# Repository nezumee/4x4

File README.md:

# 4x4 keyboard
 
The 4x4 keyboard is a modular keyboard with per-key RGB lighting intended to be used as a base for prototyping MIDI controller with QMK firmware.

It consists of the following parts:
* Head PCB with MCU and other connectors
* 1 to 4 key PCB, each having 16 hotswap Cherry MX switches in 4x4 layout

These parts can be soldered together in different configurations, resulting in different layouts, such as 4x12 Planck layout or 8x8 layout similar to MIDI drumpads controllers.

The modular design allows to iterate on parts of it without remaking a large PCB. It also makes it cost-effective to order from PCB prototyping service - ordering the typical minimum of 3 to 5 pieces of key PCB makes a single full-sized keyboard with no excessive number of spares.

PCB pieces use castellated pads to route all the signals. These pads are soldered together placing the PCBs side by side, connecting them electrically and also holding them together physically.

## Switch matrix

To allow for modularity and avoid using lots of wires to connect parts together, electrical layout of the key PCBs doesn't match their physical layout. Even though physically they are 4x4, electrically switches are laid out in 2 columns and 8 rows:
 Each key module uses the same row wires but separate columns so the full electrical layout is 8x8 if there are 4 key modules.

The column lines are routed through the key PCBs such that columns are shifted in the next connected module: if a key module is directly connected to the head, it will connect to columns 1 and 2. Module attached to the right of it will use columns 3 and 4, and so on. Attaching a module to the bottom of another shifts columns by 4 instead. The end result is that in all supported configurations, simply soldering the key modules together in the desired layout gives each of them a unique pair of column wires connected to the MCU.

Row lines are not shifted, they are passed through across the key modules as is and connect to the same MCU pin in every module.

## LED connections

WS6812 mini-e LEDs are used to provide per-key RGB. These LEDs require that they are connected in a chain to let the signal propagate from one LED to another. Within each key module, they are connected like this: 

To connect them across key modules, jumpers need to be soldered on each module to specify the side that takes LED input from previous module in the chain, and the side connecting to the next module:
* JP(L/R/T/B)I jumpers specify the left/right/top/bottom side as input
* JP(L/R/T/B)O jumpers specify the output side

This builds a chain of key modules, connecting the last LED in the preceding module to the first LED in the next:

* Input jumpers:

* Output jumpers:

## Bill of material

| Item | Quantity | Comment | Source |
| --- | --- | --- | --- |
| Head PCB | 1 | [KiCad source](pcb/headfour/) | [gerber](pcb/gerbers/headfour.zip) |
| Key PCBs | 1-4 | [KiCad source](pcb/fourbyfour/) | [gerber](pcb/gerbers/fourbyfour.zip) |
| ProMicro MCU | 1 |
| MCU socket | 1 | 2 strips of 12 pins each | https://www.digikey.com/en/products/detail/mill-max-manufacturing-corp/310-43-112-41-001000/1212186 |
| Reset tactile button | 1 | |
| TRRS jack | 1 | To support split keyboard, optional | https://boardsource.xyz/store/5eca3b7d64caf04f83aa6488 |
| Kailh MX hotswap sockets | 16-64 | | https://boardsource.xyz/store/5eca066464caf04f83aa647f |
| N4148 SOD-123 diodes | 16-64 | | https://www.digikey.com/en/products/detail/panjit-international-inc/1N4148W-R1-00001/14660400 |
| SK6812 mini-e RGB LEDs | 16-64 | Optional | https://boardsource.xyz/store/5f6316e0a2c1b43e37ca04c3 |
| Cherry MX compatible switches, keycaps | 16-64 |
| Switch plate, case | | Optional | See some example designs [here](case/)
| M2 bolts and standoffs | 8-20 |

## Build

1. Decide on the layout
    * Options: horizontal strip of 1-4, vertical strip of 2, 2x2 square  
    * Head position: any side of the key block, facing up or left    
2. Prep the PCBs
	1. Clean up the castellated edges if needed. Make sure key PCBs sit flush to each other
	2. Make sure LEDs fit in the holes, file to enlarge them if necessary
3. Solder together the PCBs pieces
	1. Use something to help hold PCBs together, like [the 3d printed holder](misc/4x4holder.stl)
        * Make sure both PCBs face the same way before soldering
        * Make sure PCBs sit flat and even as you solder, using a ruler to check they don't bend at the seam once every few soldered pads:
        
        * Tip: if using a 3D printed frame to hold PCBs, add washers before screwing the PCBs to it so plastic doesn't touch the hot contacts as you solder them
        	
	2. Turn over and clean up on the other side

4. Solder the jumpers for LED signal chaining
5. Solder the MCU socket so that you can test the rest as you go
6. Solder the per-key elements
    1. LEDs
	2. Diodes
	3. Switch hotswap sockets
7. Solder the remaining head elements
	1. TRRS jack
	2. Reset tactile button

End result:
* Top 
* Bottom 

## Firmware

This keyboard is using [QMK](https://qmk.fm/). Example layout making the keyboard work as a combination of planck keyboard and a MIDI controller is available [here](https://github.com/nezumee/qmk_firmware/tree/4x4/keyboards/4x4/keymaps/midi-controller). Note that you need [the MIDI input fix](https://github.com/qmk/qmk_firmware/pull/18654) for the MIDI feedback to work.

## Using 4x4 as a MIDI controller

QMK has MIDI support that allows using the keyboard as a MIDI controller. Per-key RGB also makes it possible to have MIDI feedback, such that each key lights up depending on the status in the DAW. For example, you can set it up that keyboard keys trigger clips or scenes, and have those keys light up in the right color when there's an active clip or when a track is armed for recording.

This support requires some integration in the DAW. Remote MIDI script for Ableton Live working with the Planck-like layout is [here](ableton_live/FourByFour).

## Known problems

* Head v1
	* There are OLED and encoder footprints, but they cannot be used since the same pins are reused for switch rows
* Brightness must be restricted when using many LEDs (48+), voltage regulator in ProMicro cannot handle them otherwise
* Split keyboard is not tested, is challenging due to LED power consumption

## License

This project is using the [MIT license](LICENSE).

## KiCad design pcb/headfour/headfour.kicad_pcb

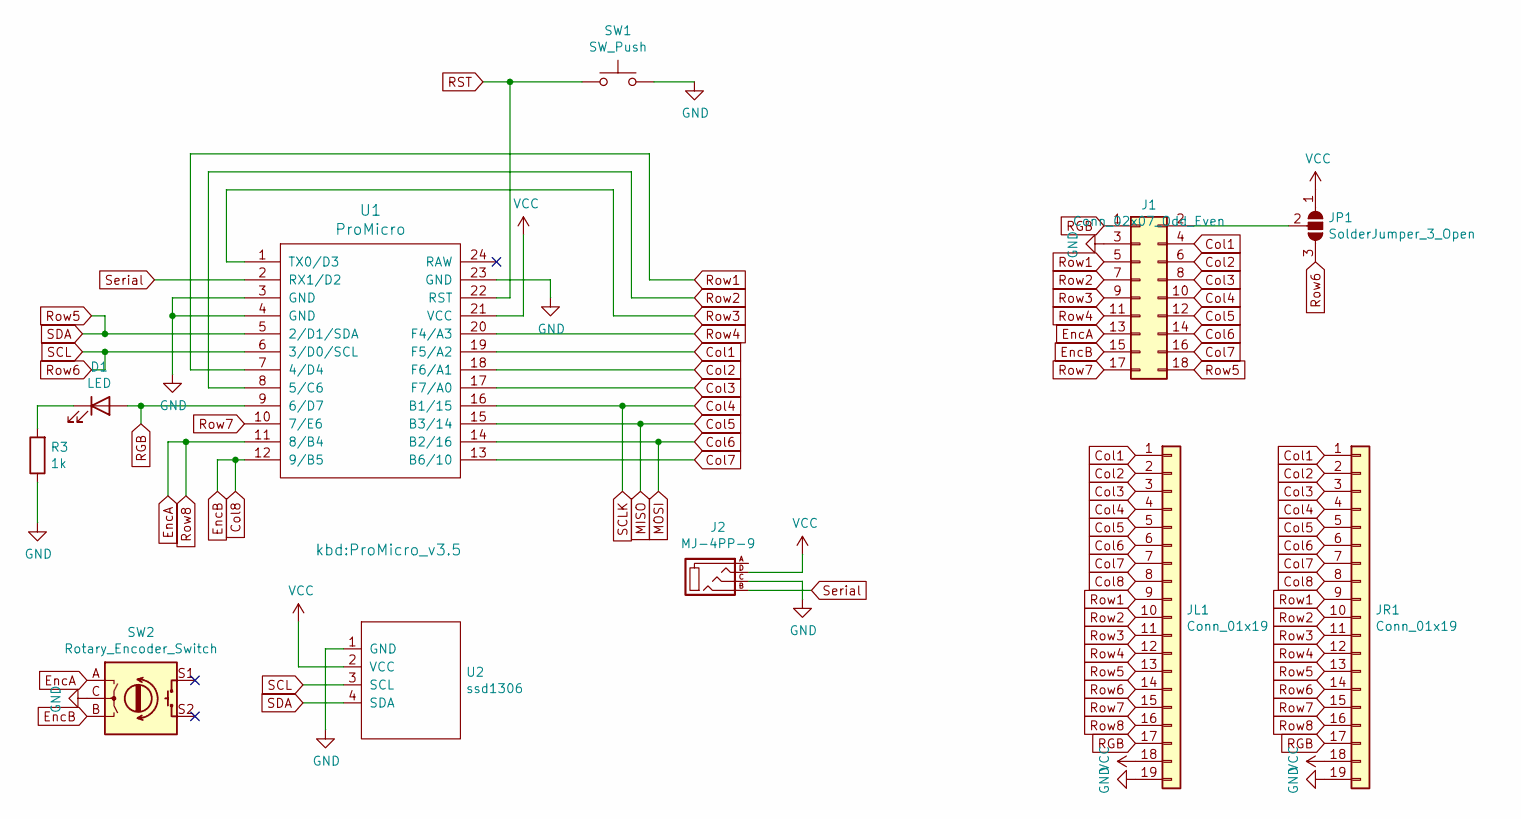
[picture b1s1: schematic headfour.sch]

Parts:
D1: LED; LED_D3.0mm
J1: Conn_02x07_Odd_Even; IDC-Header_2x09_P2.54mm_Vertical
J2: MJ-4PP-9; MJ-4PP-9_1side
JL1: Conn_01x19; PinHeader_1x19_P2.54mm_CastellatedR
JP1: SolderJumper_3_Open; SolderJumper-3_P1.3mm_Open_Pad1.0x1.5mm
JR1: Conn_01x19; PinHeader_1x19_P2.54mm_CastellatedL
R3: 1k; R_1206_3216Metric_Pad1.30x1.75mm_HandSolder
SW1: SW_Push; ResetSW_1side
SW2: Rotary_Encoder_Switch; RotaryEncoder_Alps_EC11E-Switch_Vertical_H20mm
U1: ProMicro; ProMicro_v3.5
U2: ssd1306; SSD1306

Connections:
Col1: J1.4, JL1.1, JR1.1, U1.19 (F5/A2)
Col2: J1.6, JL1.2, JR1.2, U1.18 (F6/A1)
Col3: J1.8, JL1.3, JR1.3, U1.17 (F7/A0)
Col4: J1.10, JL1.4, JR1.4, U1.16 (B1/15)
Col5: J1.12, JL1.5, JR1.5, U1.15 (B3/14)
Col6: J1.14, JL1.6, JR1.6, U1.14 (B2/16)
Col7: J1.16, JL1.7, JR1.7, U1.13 (B6/10)
Col8: J1.15, JL1.8, JR1.8, SW2.B, U1.12 (9/B5)
EncA: J1.13, JL1.16, JR1.16, SW2.A, U1.11 (8/B4)
GND: J1.3, J2.C, JL1.19, JR1.19, R3.1, SW1.2, SW2.C, U1.3 (GND), U1.4 (GND), U1.23 (GND), U2.1 (GND)
unnamed: D1.1 (K), R3.2
unnamed: J1.2, JP1.2 (C)
RGB: D1.2 (A), J1.1, JL1.17, JR1.17, U1.9 (6/D7)
RST: SW1.1, U1.22 (RST)
Row1: J1.5, JL1.9, JR1.9, U1.7 (4/D4)
Row2: J1.7, JL1.10, JR1.10, U1.8 (5/C6)
Row3: J1.9, JL1.11, JR1.11, U1.1 (TX0/D3)
Row4: J1.11, JL1.12, JR1.12, U1.20 (F4/A3)
Row5: J1.18, JL1.13, JR1.13, U1.5 (2/D1/SDA), U2.4 (SDA)
Row6: JL1.14, JP1.3 (B), JR1.14, U1.6 (3/D0/SCL), U2.3 (SCL)
Row7: J1.17, JL1.15, JR1.15, U1.10 (7/E6)
Serial: J2.B, U1.2 (RX1/D2)
VCC: J2.D, JL1.18, JP1.1 (A), JR1.18, U1.21 (VCC), U2.2 (VCC)

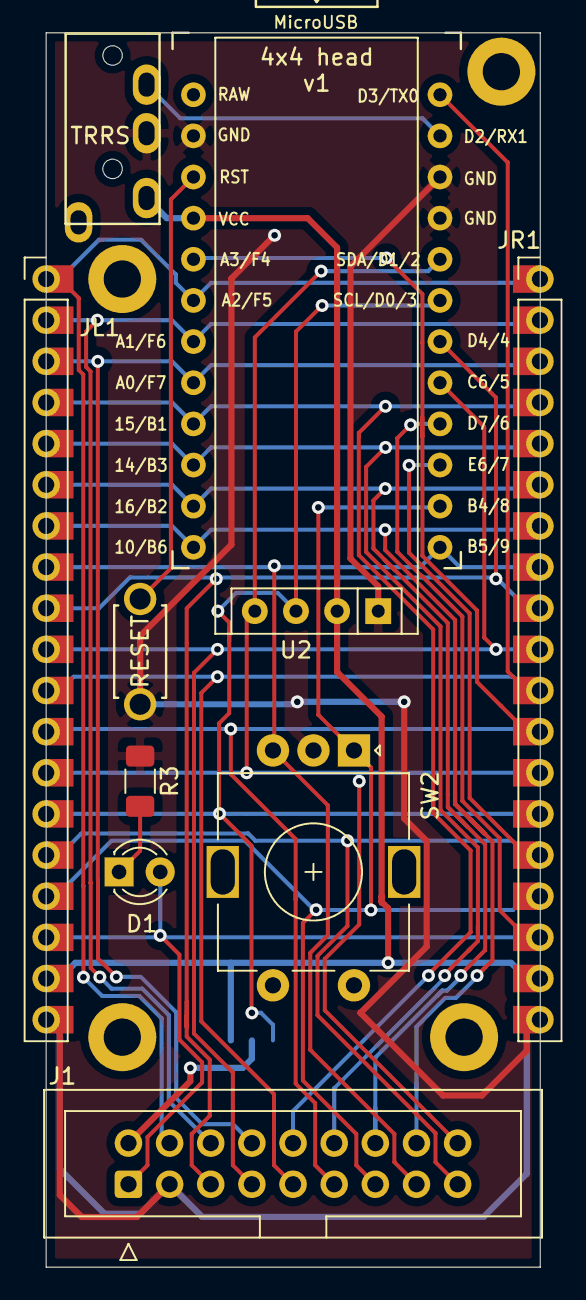
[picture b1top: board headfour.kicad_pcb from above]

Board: 2 copper layers, 30.5 x 76.2 mm, 11 parts (1 on the bottom side), 23 nets.

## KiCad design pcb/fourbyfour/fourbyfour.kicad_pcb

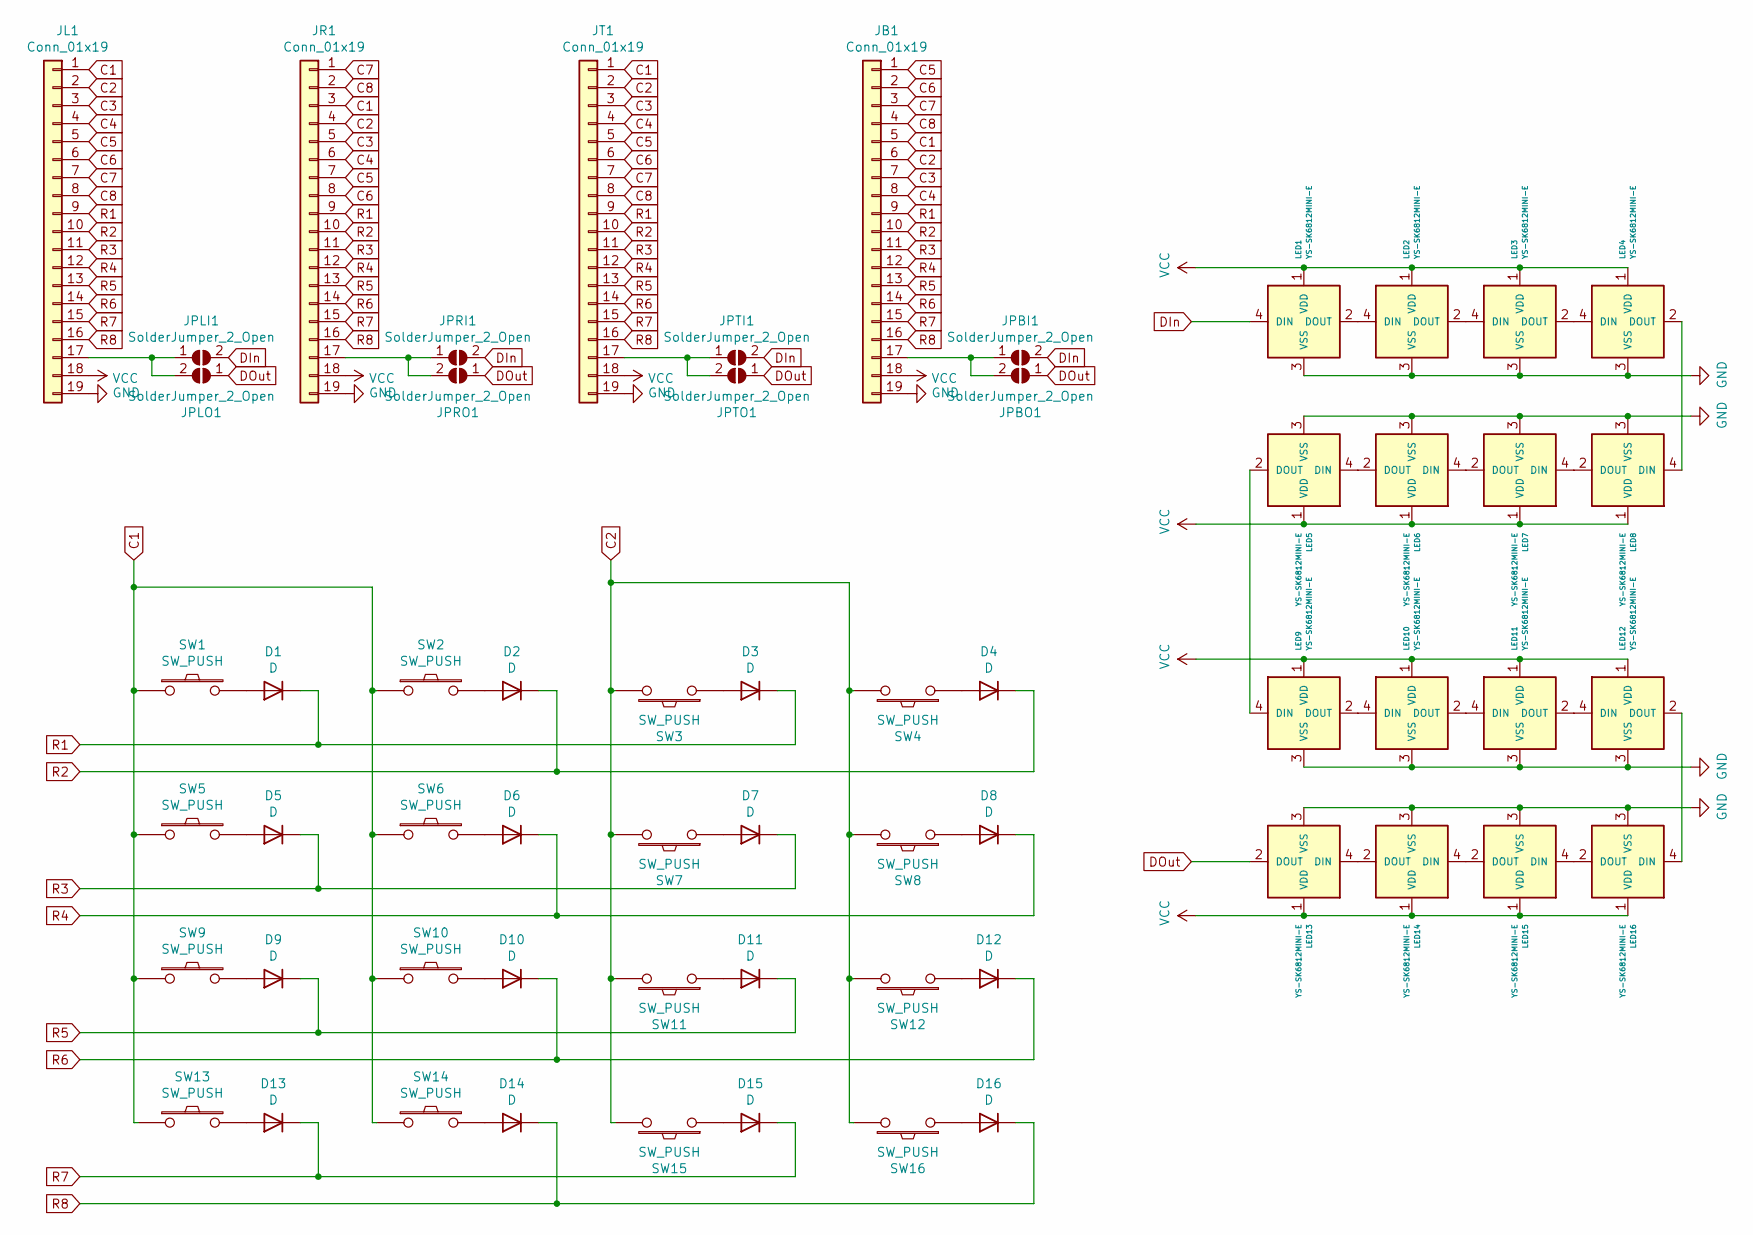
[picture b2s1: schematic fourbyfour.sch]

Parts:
D1, D2, D3, D4, D5, D6, D7, D8, D9, D10, D11, D12, D13, D14, D15, D16: D; D3_SMD_v2
JB1: Conn_01x19; PinHeader_1x19_P2.54mm_CastellatedR
JL1: Conn_01x19; PinHeader_1x19_P2.54mm_CastellatedR
JPBI1: SolderJumper_2_Open; SolderJumper-2_P1.3mm_Open_TrianglePad1.0x1.5mm
JPBO1: SolderJumper_2_Open; SolderJumper-2_P1.3mm_Open_TrianglePad1.0x1.5mm
JPLI1: SolderJumper_2_Open; SolderJumper-2_P1.3mm_Open_TrianglePad1.0x1.5mm
JPLO1: SolderJumper_2_Open; SolderJumper-2_P1.3mm_Open_TrianglePad1.0x1.5mm
JPRI1: SolderJumper_2_Open; SolderJumper-2_P1.3mm_Open_TrianglePad1.0x1.5mm
JPRO1: SolderJumper_2_Open; SolderJumper-2_P1.3mm_Open_TrianglePad1.0x1.5mm
JPTI1: SolderJumper_2_Open; SolderJumper-2_P1.3mm_Open_TrianglePad1.0x1.5mm
JPTO1: SolderJumper_2_Open; SolderJumper-2_P1.3mm_Open_TrianglePad1.0x1.5mm
JR1: Conn_01x19; PinHeader_1x19_P2.54mm_CastellatedL
JT1: Conn_01x19; PinHeader_1x19_P2.54mm_CastellatedL
LED1, LED2, LED3, LED4, LED5, LED6, LED7, LED8, LED9, LED10, LED11, LED12, LED13, LED14, LED15, LED16: YS-SK6812MINI-E
SW1, SW2, SW3, SW4, SW5, SW6, SW7, SW8, SW9, SW10, SW11, SW12, SW13, SW14, SW15, SW16: SW_PUSH; CherryMX_Hotswap

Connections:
C1: JB1.5, JL1.1, JR1.3, JT1.1, SW1.1, SW2.1, SW5.1, SW6.1, SW9.1, SW10.1, SW13.1, SW14.1
C2: JB1.6, JL1.2, JR1.4, JT1.2, SW3.2, SW4.2, SW7.2, SW8.2, SW11.2, SW12.2, SW15.2, SW16.2
C3: JB1.7, JL1.3, JR1.5, JT1.3
C4: JB1.8, JL1.4, JR1.6, JT1.4
C5: JB1.1, JL1.5, JR1.7, JT1.5
C6: JB1.2, JL1.6, JR1.8, JT1.6
C7: JB1.3, JL1.7, JR1.1, JT1.7
C8: JB1.4, JL1.8, JR1.2, JT1.8
DIn: JPBI1.2 (B), JPLI1.2 (B), JPRI1.2 (B), JPTI1.2 (B), LED1.4 (DIN)
DOut: JPBO1.1 (A), JPLO1.1 (A), JPRO1.1 (A), JPTO1.1 (A), LED13.2 (DOUT)
GND: JB1.19, JL1.19, JR1.19, JT1.19, LED1.3 (VSS), LED2.3 (VSS), LED3.3 (VSS), LED4.3 (VSS), LED5.3 (VSS), LED6.3 (VSS), LED7.3 (VSS), LED8.3 (VSS), LED9.3 (VSS), LED10.3 (VSS), LED11.3 (VSS), LED12.3 (VSS), LED13.3 (VSS), LED14.3 (VSS), LED15.3 (VSS), LED16.3 (VSS)
unnamed: D1.2 (A), SW1.2
unnamed: D2.2 (A), SW2.2
unnamed: D3.2 (A), SW3.1
unnamed: D4.2 (A), SW4.1
unnamed: D5.2 (A), SW5.2
unnamed: D6.2 (A), SW6.2
unnamed: D7.2 (A), SW7.1
unnamed: D8.2 (A), SW8.1
unnamed: D9.2 (A), SW9.2
unnamed: D10.2 (A), SW10.2
unnamed: D11.2 (A), SW11.1
unnamed: D12.2 (A), SW12.1
unnamed: D13.2 (A), SW13.2
unnamed: D14.2 (A), SW14.2
unnamed: D15.2 (A), SW15.1
unnamed: D16.2 (A), SW16.1
unnamed: JB1.17, JPBI1.1 (A), JPBO1.2 (B)
unnamed: JL1.17, JPLI1.1 (A), JPLO1.2 (B)
unnamed: JPRI1.1 (A), JPRO1.2 (B), JR1.17
unnamed: JPTI1.1 (A), JPTO1.2 (B), JT1.17
unnamed: LED1.2 (DOUT), LED2.4 (DIN)
unnamed: LED2.2 (DOUT), LED3.4 (DIN)
unnamed: LED3.2 (DOUT), LED4.4 (DIN)
unnamed: LED4.2 (DOUT), LED8.4 (DIN)
unnamed: LED5.2 (DOUT), LED9.4 (DIN)
unnamed: LED5.4 (DIN), LED6.2 (DOUT)
unnamed: LED6.4 (DIN), LED7.2 (DOUT)
unnamed: LED7.4 (DIN), LED8.2 (DOUT)
unnamed: LED10.2 (DOUT), LED11.4 (DIN)
unnamed: LED9.2 (DOUT), LED10.4 (DIN)
unnamed: LED11.2 (DOUT), LED12.4 (DIN)
unnamed: LED12.2 (DOUT), LED16.4 (DIN)
unnamed: LED13.4 (DIN), LED14.2 (DOUT)
unnamed: LED14.4 (DIN), LED15.2 (DOUT)
unnamed: LED15.4 (DIN), LED16.2 (DOUT)
R1: D1.1 (K), D3.1 (K), JB1.9, JL1.9, JR1.9, JT1.9
R2: D2.1 (K), D4.1 (K), JB1.10, JL1.10, JR1.10, JT1.10
R3: D5.1 (K), D7.1 (K), JB1.11, JL1.11, JR1.11, JT1.11
R4: D6.1 (K), D8.1 (K), JB1.12, JL1.12, JR1.12, JT1.12
R5: D9.1 (K), D11.1 (K), JB1.13, JL1.13, JR1.13, JT1.13
R6: D10.1 (K), D12.1 (K), JB1.14, JL1.14, JR1.14, JT1.14
R7: D13.1 (K), D15.1 (K), JB1.15, JL1.15, JR1.15, JT1.15
R8: D14.1 (K), D16.1 (K), JB1.16, JL1.16, JR1.16, JT1.16
VCC: JB1.18, JL1.18, JR1.18, JT1.18, LED1.1 (VDD), LED2.1 (VDD), LED3.1 (VDD), LED4.1 (VDD), LED5.1 (VDD), LED6.1 (VDD), LED7.1 (VDD), LED8.1 (VDD), LED9.1 (VDD), LED10.1 (VDD), LED11.1 (VDD), LED12.1 (VDD), LED13.1 (VDD), LED14.1 (VDD), LED15.1 (VDD), LED16.1 (VDD)

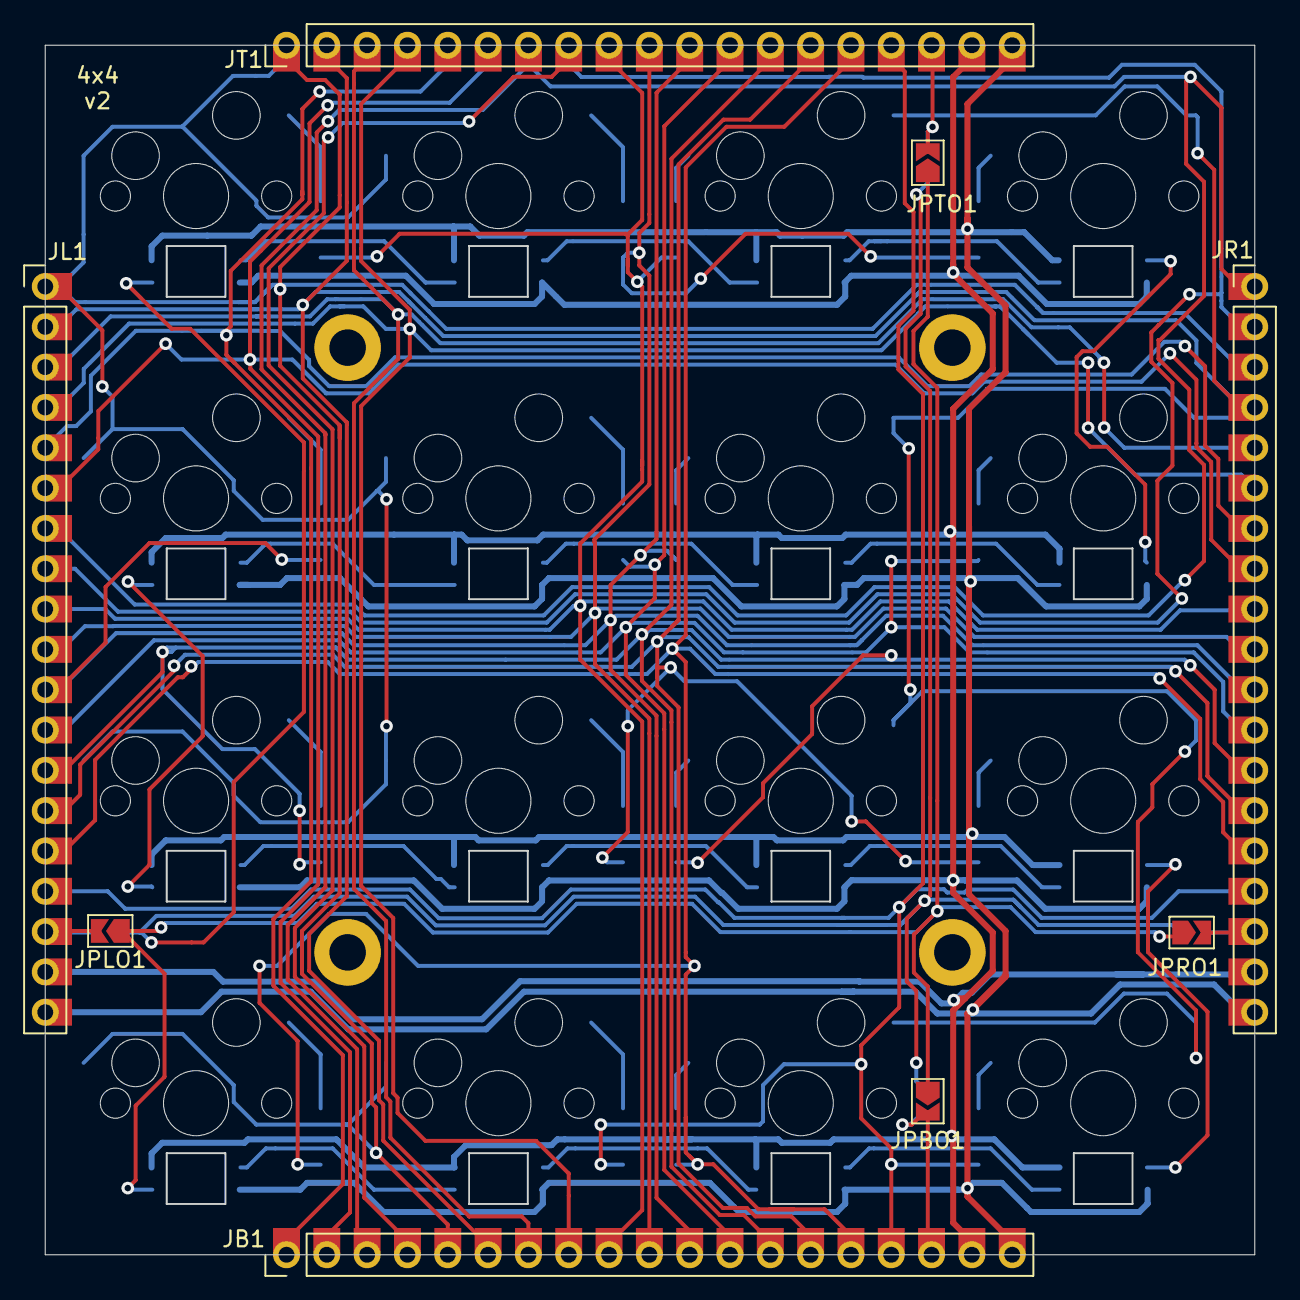
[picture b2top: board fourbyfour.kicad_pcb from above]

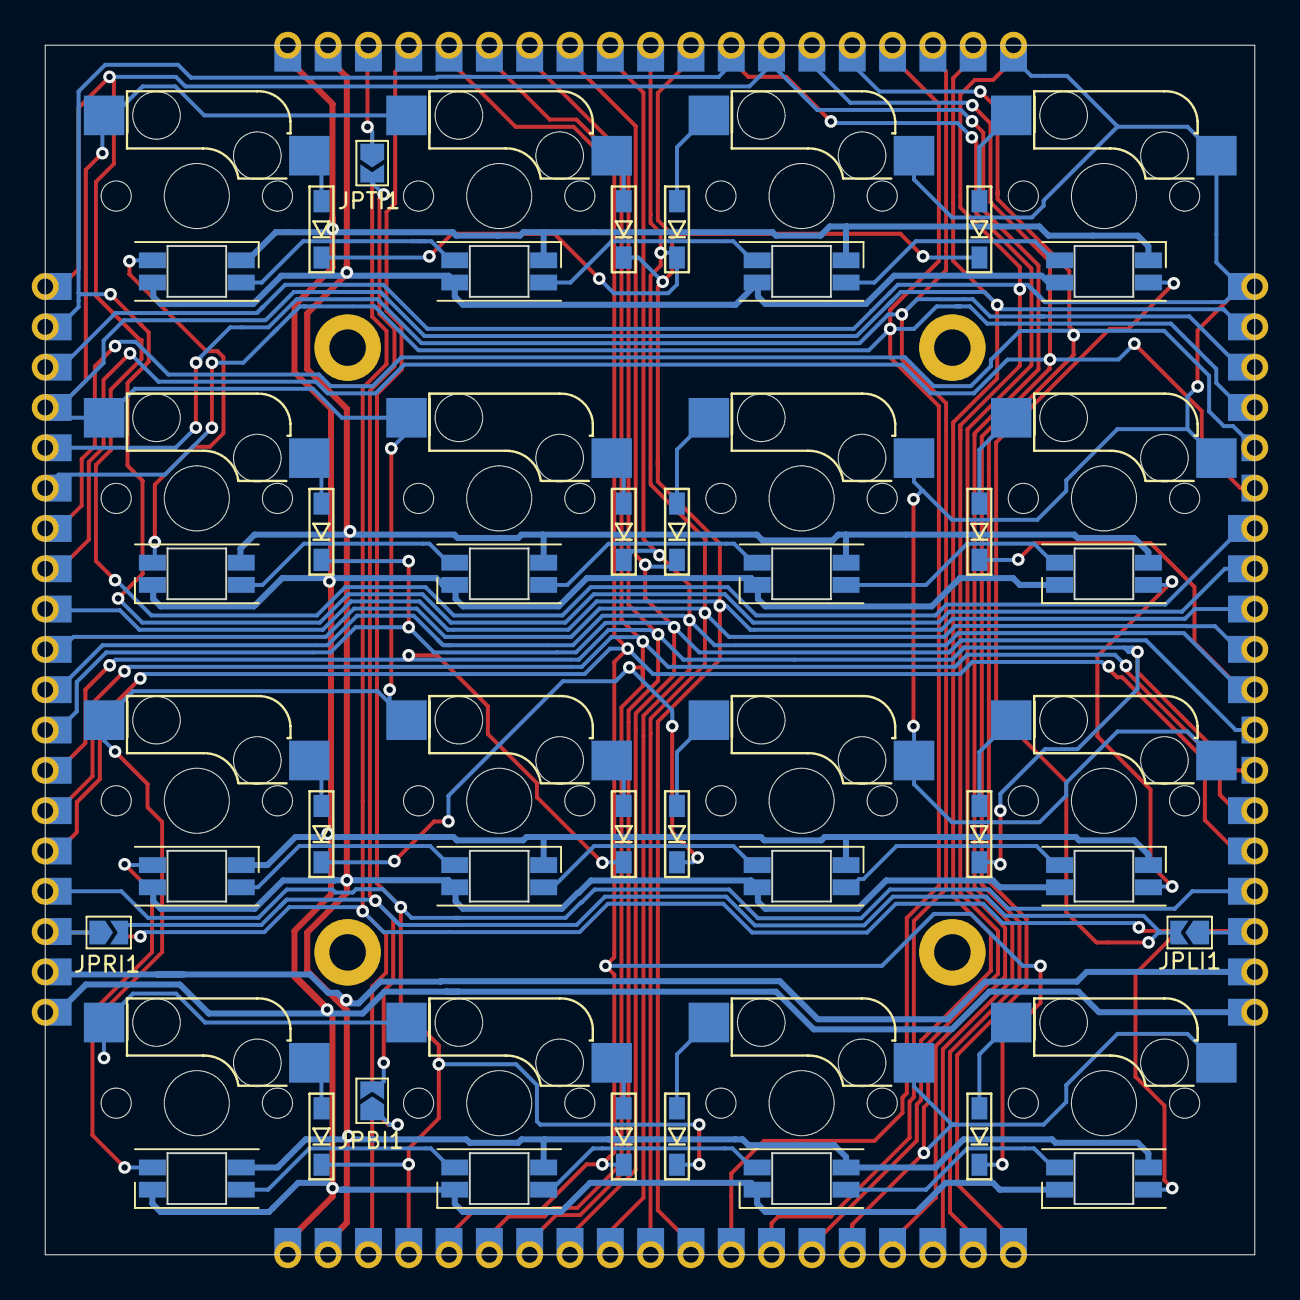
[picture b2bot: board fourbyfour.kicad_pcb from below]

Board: 2 copper layers, 76.1 x 76.1 mm, 60 parts (36 on the bottom side), 55 nets.

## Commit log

2022-11-12 Add Ableton live scripts
2022-11-12 Add 3d printed files
2022-11-12 Add foostan kbd submodule
2022-11-12 Add key module PCB
2022-11-12 Update gerber path
2022-11-12 Add the head PCB
2022-11-12 Add readme content
2022-11-12 Add a picture of keyboard with Ableton Live
2022-11-13 Add finished square picture, clean up the readme
2022-11-13 Reference the MIDI script source
2022-11-13 Add references to gerbers
